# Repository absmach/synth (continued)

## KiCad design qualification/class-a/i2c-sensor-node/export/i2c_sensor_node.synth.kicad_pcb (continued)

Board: 2 copper layers, 57 parts (0 on the bottom side), 35 nets, no tracks yet.

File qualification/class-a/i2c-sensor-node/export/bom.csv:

refdes,value,kind,description,kicad_symbol,kicad_footprint,lcsc_pn,mpn
C1,10uF,capacitor,"Generic 0805 MLCC, X7R/X5R, any value",Device:C,Capacitor_SMD:C_0805_2012Metric,,
C10,100nF,capacitor,"Generic 0603 MLCC, X7R/X5R, any value",Device:C,Capacitor_SMD:C_0603_1608Metric,,
C11,100nF,capacitor,"Generic 0603 MLCC, X7R/X5R, any value",Device:C,Capacitor_SMD:C_0603_1608Metric,,
C12,100nF,capacitor,"Generic 0603 MLCC, X7R/X5R, any value",Device:C,Capacitor_SMD:C_0603_1608Metric,,
C2,10uF,capacitor,"Generic 0805 MLCC, X7R/X5R, any value",Device:C,Capacitor_SMD:C_0805_2012Metric,,
C3,47uF,capacitor,"47µF 16V tantalum capacitor, polarised, 3528 case",Device:C_Polarized,Capacitor_Tantalum_SMD:CP_EIA-3528-21_Kemet-B,,
C4,10uF,capacitor,"Generic 0805 MLCC, X7R/X5R, any value",Device:C,Capacitor_SMD:C_0805_2012Metric,,
C5,100nF,capacitor,"Generic 0603 MLCC, X7R/X5R, any value",Device:C,Capacitor_SMD:C_0603_1608Metric,,
C6,100nF,capacitor,"Generic 0603 MLCC, X7R/X5R, any value",Device:C,Capacitor_SMD:C_0603_1608Metric,,
C7,4.7uF,capacitor,"Generic 0603 MLCC, X7R/X5R, any value",Device:C,Capacitor_SMD:C_0603_1608Metric,,
C8,100nF,capacitor,"Generic 0603 MLCC, X7R/X5R, any value",Device:C,Capacitor_SMD:C_0603_1608Metric,,
D1,1N5819,diode,"Diodes Inc. 1N5819HW-7-F, 40 V 1 A Schottky diode, SOD-123, low forward voltage",Device:D_Schottky,Diode_SMD:D_SOD-123,C82544,1N5819HW-7-F
D10,3.3V zener,diode,"3.3V Zener diode, SOD-123",Device:D_Zener,Diode_SMD:D_SOD-123,,
D11,3.3V zener,diode,"3.3V Zener diode, SOD-123",Device:D_Zener,Diode_SMD:D_SOD-123,,
D12,3.3V zener,diode,"3.3V Zener diode, SOD-123",Device:D_Zener,Diode_SMD:D_SOD-123,,
D13,3.3V zener,diode,"3.3V Zener diode, SOD-123",Device:D_Zener,Diode_SMD:D_SOD-123,,
D14,1N5819,diode,"Diodes Inc. 1N5819HW-7-F, 40 V 1 A Schottky diode, SOD-123, low forward voltage",Device:D_Schottky,Diode_SMD:D_SOD-123,C82544,1N5819HW-7-F
D15,GREEN,diode,"Lite-On LTST-C190KGKT green AlInGaP LED, 0603, Vf 1.9 to 2.4V at 20mA",Device:LED,LED_SMD:LED_0603_1608Metric,,LTST-C190KGKT
D19,3.3V zener,diode,"3.3V Zener diode, SOD-123",Device:D_Zener,Diode_SMD:D_SOD-123,,
D20,3.3V zener,diode,"3.3V Zener diode, SOD-123",Device:D_Zener,Diode_SMD:D_SOD-123,,
D21,3.3V zener,diode,"3.3V Zener diode, SOD-123",Device:D_Zener,Diode_SMD:D_SOD-123,,
D22,3.3V zener,diode,"3.3V Zener diode, SOD-123",Device:D_Zener,Diode_SMD:D_SOD-123,,
D23,3.3V zener,diode,"3.3V Zener diode, SOD-123",Device:D_Zener,Diode_SMD:D_SOD-123,,
D24,3.3V zener,diode,"3.3V Zener diode, SOD-123",Device:D_Zener,Diode_SMD:D_SOD-123,,
D4,PTVS6V0S1UR,diode,"Nexperia PTVS6V0S1UR 400 W unidirectional TVS, 6.0 V standoff, SOD123W, for VBUS and CC",Device:D_Zener,Diode_SMD:Nexperia_CFP3_SOD-123W,,PTVS6V0S1UR
D7,3.3V zener,diode,"3.3V Zener diode, SOD-123",Device:D_Zener,Diode_SMD:D_SOD-123,,
D8,3.3V zener,diode,"3.3V Zener diode, SOD-123",Device:D_Zener,Diode_SMD:D_SOD-123,,
D9,3.3V zener,diode,"3.3V Zener diode, SOD-123",Device:D_Zener,Diode_SMD:D_SOD-123,,
F1,0.5A hold,fuse,"Resettable polyfuse (PPTC), 0.5 A hold, 2-pin, 1812. Generic: MPN needs sourcing.",Device:Polyfuse,Fuse:Fuse_1812_4532Metric,,
H2,(no value),mounting_hole,M2.5 non-plated mounting hole (NPTH) for a board corner,Mechanical:MountingHole,MountingHole:MountingHole_2.5mm,,
H3,(no value),mounting_hole,M2.5 non-plated mounting hole (NPTH) for a board corner,Mechanical:MountingHole,MountingHole:MountingHole_2.5mm,,
J1,JST S2B-XH-A-1,connector,"JST XH-series 2-pin wire-to-board connector, 2.0mm pitch",Connector_Generic:Conn_01x02,Connector_JST:JST_XH_S2B-XH-A-1_1x02_P2.50mm_Horizontal,,
J3,JST S4B-PH-K-S,connector,"JST PH-series 4-pin wire-to-board connector, 2.0mm pitch",Connector_Generic:Conn_01x04,Connector_JST:JST_PH_S4B-PH-K_1x04_P2.00mm_Horizontal,,
J4,SWD,connector,"1x5 through-hole pin header, 2.54 mm pitch (SWD); datasheet_url is the product page of the Harwin M20 series, no manufacturer PDF link was verifiable",Connector_Generic:Conn_01x05,Connector_PinHeader_2.54mm:PinHeader_1x05_P2.54mm_Vertical,,
J5,GPIO,connector,"1x12 through-hole pin header, 2.54 mm pitch (GPIO); datasheet_url is the product page of the Harwin M20 series, no manufacturer PDF link was verifiable",Connector_Generic:Conn_01x12,Connector_PinHeader_2.54mm:PinHeader_1x12_P2.54mm_Vertical,,
R10,4.7k,resistor,"Generic 0603 thick-film resistor, any value",Device:R_US,Resistor_SMD:R_0603_1608Metric,,
R11,330,resistor,"Generic 0603 thick-film resistor, any value",Device:R_US,Resistor_SMD:R_0603_1608Metric,,
R12,1k,resistor,"Generic 0603 thick-film resistor, any value",Device:R_US,Resistor_SMD:R_0603_1608Metric,,
R13,100,resistor,"Generic 0603 thick-film resistor, any value",Device:R_US,Resistor_SMD:R_0603_1608Metric,,
R14,100,resistor,"Generic 0603 thick-film resistor, any value",Device:R_US,Resistor_SMD:R_0603_1608Metric,,
R15,330,resistor,"Generic 0603 thick-film resistor, any value",Device:R_US,Resistor_SMD:R_0603_1608Metric,,
R16,330,resistor,"Generic 0603 thick-film resistor, any value",Device:R_US,Resistor_SMD:R_0603_1608Metric,,
R17,330,resistor,"Generic 0603 thick-film resistor, any value",Device:R_US,Resistor_SMD:R_0603_1608Metric,,
R18,330,resistor,"Generic 0603 thick-film resistor, any value",Device:R_US,Resistor_SMD:R_0603_1608Metric,,
R19,330,resistor,"Generic 0603 thick-film resistor, any value",Device:R_US,Resistor_SMD:R_0603_1608Metric,,
R20,330,resistor,"Generic 0603 thick-film resistor, any value",Device:R_US,Resistor_SMD:R_0603_1608Metric,,
R21,330,resistor,"Generic 0603 thick-film resistor, any value",Device:R_US,Resistor_SMD:R_0603_1608Metric,,
R22,330,resistor,"Generic 0603 thick-film resistor, any value",Device:R_US,Resistor_SMD:R_0603_1608Metric,,
R23,100,resistor,"Generic 0805 thick-film resistor, any value",Device:R_US,Resistor_SMD:R_0805_2012Metric,,
R24,680,resistor,"Generic 0603 thick-film resistor, any value",Device:R_US,Resistor_SMD:R_0603_1608Metric,,
R3,10k,resistor,"Generic 0603 thick-film resistor, any value",Device:R_US,Resistor_SMD:R_0603_1608Metric,,
R9,4.7k,resistor,"Generic 0603 thick-film resistor, any value",Device:R_US,Resistor_SMD:R_0603_1608Metric,,
SW1,RESET,switch,Generic SPST tactile button,Switch:SW_Push,Button_Switch_SMD:SW_SPST_PTS645Sx43SMTR92,,
U1,AMS1117-3.3,regulator,"AMS1117-3.3 fixed 3.3V LDO regulator, SOT-223 — common JLC stock",Regulator_Linear:AMS1117-3.3,Package_TO_SOT_SMD:SOT-223-3_TabPin2,C6186,AMS1117-3.3
U2,STM32G030F6P6,mcu,"STMicro STM32G030F6P6 Cortex-M0+ 64 MHz, 32 KB flash, 8 KB RAM, TSSOP-20. Pin map checked against KiCad MCU_ST_STM32G0:STM32G030F6Px",MCU_ST_STM32G0:STM32G030F6Px,Package_SO:TSSOP-20_4.4x6.5mm_P0.65mm,,STM32G030F6P6
U3,BME680,sensor,"Bosch BME680 T/RH/P/gas sensor, 3.0x3.0 mm 8-pin LGA, I2C/SPI. Pins checked against KiCad Sensor:BME680; footprint is the 3x3 mm 0.8 mm pitch one whose KiCad description cites the BME680 datasheet",Sensor:BME680,Package_LGA:Bosch_LGA-8_3x3mm_P0.8mm_ClockwisePinNumbering,,BME680
U5,24LC256-I/SN,memory,"Microchip 24LC256-I/SN 256 Kbit I2C EEPROM, SOIC-8. Pin map checked against KiCad Memory_EEPROM:24LC256",Memory_EEPROM:24LC256,Package_SO:SOIC-8_3.9x4.9mm_P1.27mm,C411625,24LC256-I/SN

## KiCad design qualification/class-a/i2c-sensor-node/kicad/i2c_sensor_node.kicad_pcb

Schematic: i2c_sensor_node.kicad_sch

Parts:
C1, C2, C4: 10uF; C_0805_2012Metric
C3: 47uF; CP_EIA-3528-21_Kemet-B
C5, C6, C8, C9, C10, C11, C12, C14: 100nF; C_0603_1608Metric
C7, C13: 4.7uF; C_0603_1608Metric
D1, D2, D14: 1N5819; D_SOD-123; MPN 1N5819; LCSC C8224
D3, D4: PTVS6V0S1UR; Nexperia_CFP3_SOD-123W; MPN PTVS6V0S1UR
D5, D6, D7, D8, D9, D10, D11, D12, D13: PRTR5V0U2X; SOT-143; MPN PRTR5V0U2X
D15: GREEN; LED_0603_1608Metric; MPN 0603-GREEN; LCSC C72043
D16: AMBER; LED_0603_1608Metric
D17: RED; LED_0603_1608Metric; MPN 0603-RED; LCSC C2286
D18: GREEN; LED_0603_1608Metric; MPN LTST-C190KGKT
F1, F2: 0.5A hold; Fuse_Bourns_MF-RG300
H1, H2, H3, H4: (no value); MountingHole_2.5mm
J1: JST S2B-XH-A-1; JST_XH_S2B-XH-A-1_1x02_P2.50mm_Horizontal
J2: TYPE-C-31-M-12; USB_C_Receptacle_HRO_TYPE-C-31-M-12; MPN TYPE-C-31-M-12; LCSC C165948
J3: JST S4B-PH-K-S; JST_PH_S4B-PH-K_1x04_P2.00mm_Horizontal
J4: SWD; PinHeader_1x05_P2.54mm_Vertical
J5: GPIO; PinHeader_1x12_P2.54mm_Vertical
Q1: IRLML6244; SOT-23
R1, R2: 5.1k; R_0603_1608Metric
R3, R6, R28: 10k; R_0603_1608Metric
R4, R7, R12, R26, R27: 1k; R_0603_1608Metric
R5, R8: 100k; R_0603_1608Metric
R9, R10: 4.7k; R_0603_1608Metric
R11, R15, R16, R17, R18, R19, R20, R21, R22: 330; R_0603_1608Metric
R13, R14: 100; R_0603_1608Metric
R23: 100; R_0805_2012Metric
R24, R25: 680; R_0603_1608Metric
SW1: RESET; SW_SPST_PTS645Sx43SMTR92
TP1: +5V_PROT; TestPoint_Pad_D1.5mm
TP2: +3V3; TestPoint_Pad_D1.5mm
TP3, TP9: GND; TestPoint_Pad_D1.5mm
TP4: I2C_SDA; TestPoint_Pad_D1.5mm
TP5: I2C_SCL; TestPoint_Pad_D1.5mm
TP6: UART_TX; TestPoint_Pad_D1.5mm
TP7: UART_RX; TestPoint_Pad_D1.5mm
TP8: VIN_FUSED; TestPoint_Pad_D1.5mm
U1: AMS1117-3.3; SOT-223-3_TabPin2; MPN AMS1117-3.3; LCSC C6186
U2: STM32G030F6P6; TSSOP-20_4.4x6.5mm_P0.65mm; MPN STM32G030F6P6
U3: BME680; Bosch_LGA-8_3x3mm_P0.8mm_ClockwisePinNumbering; MPN BME680
U4: CH340C; SOIC-16_3.9x9.9mm_P1.27mm; MPN CH340C
U5: 24LC256-I/SN; SOIC-8_3.9x4.9mm_P1.27mm; MPN 24LC256-I/SN; LCSC C7611

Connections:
3V3_REF: J3.4, J4.1, J5.1, R23.2
+3V3: C3.1, C4.1, C5.1, C6.1, C7.1, C9.1, C10.1, C11.1, C12.1, D7.4 (VCC), D8.4 (VCC), D9.4 (VCC), D10.4 (VCC), D11.4 (VCC), D12.4 (VCC), D13.4 (VCC), D14.2 (A), R3.1, R5.1, R6.1, R9.1, R10.1, R24.1, R26.1, R27.1, R28.1, TP2.1, U1.2 (VO), U2.4 (VDD), U3.2 (CSB), U3.6 (VDDIO), U3.8 (VDD), U4.4 (V3), U4.16 (VCC), U5.8 (VCC)
+5V_PROT: C1.1, C2.1, D1.1 (K), D2.1 (K), D4.1 (K), TP1.1, U1.3 (VI)
BOOT_DRV: Q1.3 (D), R6.2, R7.1
BRIDGE_RXD: D18.1 (K), U2.16 (PA9/PA11), U4.3 (RXD)
BRIDGE_TXD: D17.1 (K), U2.17 (PA10/PA12), U4.2 (TXD)
CH340_STRAP: R28.2, U4.9 (~CTS), U4.10 (~DSR), U4.11 (~RI), U4.12 (~DCD), U4.15 (R232)
DTR_N: R4.1, U4.13 (~DTR)
GND: C1.2, C2.2, C3.2, C4.2, C5.2, C6.2, C7.2, C8.2, C9.2, C10.2, C11.2, C12.2, C13.2, C14.2, D3.2 (A), D4.2 (A), D5.1 (GND), D6.1 (GND), D7.1 (GND), D8.1 (GND), D9.1 (GND), D10.1 (GND), D11.1 (GND), D12.1 (GND), D13.1 (GND), D15.1 (K), D16.1 (K), J1.2, J2.A1 (GND), J2.A12 (GND), J2.B1 (GND), J2.B12 (GND), J2.SH (SHIELD), J3.1, J4.4, J5.2, J5.6, J5.10, Q1.2 (S), R1.2, R2.2, R8.2, SW1.2, TP3.1, TP9.1, U1.1 (GND), U2.5 (VSS), U3.1 (GND), U3.5 (SDO), U3.7 (GND), U4.1 (GND), U5.1 (A0), U5.2 (A1), U5.3 (A2), U5.4 (GND), U5.7 (WP)
GPIO_PA0: D10.2 (I/O1), J5.3, R15.2
GPIO_PA0_MCU: R15.1, U2.7 (PA0)
GPIO_PA1: D10.3 (I/O2), J5.4, R16.2
GPIO_PA1_MCU: R16.1, U2.8 (PA1)
GPIO_PA4: D11.2 (I/O1), J5.5, R17.2
GPIO_PA4_MCU: R17.1, U2.11 (PA4)
GPIO_PA5: D11.3 (I/O2), J5.7, R18.2
GPIO_PA5_MCU: R18.1, U2.12 (PA5)
GPIO_PA6: D12.2 (I/O1), J5.8, R19.2
GPIO_PA6_MCU: R19.1, U2.13 (PA6)
GPIO_PA7: D12.3 (I/O2), J5.9, R20.2
GPIO_PA7_MCU: R20.1, U2.14 (PA7)
GPIO_PB0: D13.2 (I/O1), J5.11, R21.2
GPIO_PB0_MCU: R21.1, U2.15 (PA8/PB0/PB1/PB2)
GPIO_PB9: D13.3 (I/O2), J5.12, R22.2
GPIO_PB9_MCU: R22.1, U2.2 (PB9/PC14)
I2C_SCL: R10.2, TP5.1, U2.20 (PB3/PB4/PB5/PB6), U3.4 (SCK), U5.6 (SCL)
I2C_SDA: R9.2, TP4.1, U2.1 (PB7/PB8), U3.3 (SDI), U5.5 (SDA)
LED_PWR: D15.2 (A), R24.2
LED_RXA: D18.2 (A), R27.2
LED_STATUS: R25.1, U2.3 (PC15)
LED_STATUS_A: D16.2 (A), R25.2
LED_TXA: D17.2 (A), R26.2
NRST: C8.1, D9.2 (I/O1), J4.5, R3.2, R4.2, SW1.1, U2.6 (NRST)
REF_D: D14.1 (K), R23.1
RTS_N: Q1.1 (G), R5.2, U4.14 (~RTS)
SWCLK: D8.3 (I/O2), J4.3, R14.2
SWCLK_MCU: R7.2, R8.1, R14.1, U2.19 (PA14/PA15)
SWDIO: D8.2 (I/O1), J4.2, R13.2
SWDIO_MCU: R13.1, U2.18 (PA13)
U2_RX: R12.1, U2.10 (PA3)
U2_TX: R11.1, U2.9 (PA2)
UART_RX: D7.3 (I/O2), J3.3, R12.2, TP7.1
UART_TX: D7.2 (I/O1), J3.2, R11.2, TP6.1
USB_CC1: D6.2 (I/O1), J2.A5 (CC1), R1.1
USB_CC2: D6.3 (I/O2), J2.B5 (CC2), R2.1
USB_DN: D5.3 (I/O2), J2.A7 (D-), J2.B7 (D-), U4.6 (UD-)
USB_DP: D5.2 (I/O1), J2.A6 (D+), J2.B6 (D+), U4.5 (UD+)
VBUS_FUSED: C13.1, D2.2 (A), F2.2
VBUS_USB: C14.1, D3.1 (K), D5.4 (VCC), D6.4 (VCC), F2.1, J2.A4 (VBUS), J2.A9 (VBUS), J2.B4 (VBUS), J2.B9 (VBUS)
VIN_5V_FUSED: D1.2 (A), F1.2, TP8.1
VIN_5V_RAW: F1.1, J1.1

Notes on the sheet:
5V INPUT: FUSE THEN DIODE
USB-C
3V3 REGULATOR
STM32G030 MCU
USB BRIDGE
I2C SENSING
UART BREAKOUT
GPIO HEADER
TEST POINTS
J1 pin 1 = +5 V, pin 2 = GND. Mates with JST XHP-2 housing.
Order: fuse first (fault current meets a limiter), diode second (reversed supply meets a blocker).
D4 clamps transients on +5V_PROT, behind D1 so a reversed supply never forward-biases it.
CC1/CC2 5.1k to GND: advertises a 5 V sink. D5 guards D+/D-, D6 the CC pins, D3 VBUS.
D2 ORs VBUS onto +5V_PROT and blocks back-feed into the host port.
Two sources: the higher of the two diode-OR inputs supplies the board; neither is back-fed.
AMS1117 tab is VOUT (pin 2): the tab pad is the +3V3 copper area.
Power LED: (3.3 V - 2.2 V) / 680 R = 1.6 mA.
J4: 1 = 3V3_REF (sense only), 2 = SWDIO, 3 = SWCLK, 4 = GND, 5 = NRST.
PA14 is SWCLK and BOOT0. Default option bytes (nBOOT_SEL=1) ignore the pin; blank flash enters the ROM bootloader.
Status LED on PC15: (3.3 - 2.0) / 680 = 1.9 mA.
CH340C has an internal oscillator: no crystal. VCC = V3 = 3.3 V.
CTS, DSR, RI, DCD and R232 are tied high through R28 (modem lines unused).
DTR (active low) pulls NRST low through 1k. RTS asserted (low) turns Q1 off and BOOT0 rises to 3.3 V.
Idle RTS is high, Q1 on, BOOT0 low: boots flash with the bridge attached or not.
D17 lights on host-to-MCU data, D18 on MCU-to-host data.
BME680 SDO low = 0x76, CSB high = I2C. 24LC256 A2:A0 low = 0x50. No collision.
One pull-up pair, 4.7k each, for the whole bus.
J3: 1 GND, 2 UART_TX (MCU out), 3 UART_RX (MCU in), 4 3V3_REF (sense only, 3 mA max).
Host must use 3.3 V logic. Clamp to +3V3 + one diode drop (about 4.0 V) and to GND - 0.7 V.
J5: 1 3V3_REF, 2 GND, 3 PA0, 4 PA1, 5 PA4, 6 GND, 7 PA5, 8 PA6, 9 PA7, 10 GND, 11 PB0, 12 PB9.
3V3_REF = +3V3 through D14 (blocks back-drive) and 100R: sense or reference only, 3 mA max (about 2.7 V at 3 mA), 30 mA into a short.
TP1 +5V_PROT, TP2 +3V3, TP3/TP9 GND, TP4 I2C_SDA, TP5 I2C_SCL, TP6 UART_TX, TP7 UART_RX, TP8 VIN_5V_FUSED.
H1-H4: M2.5 non-plated mounting holes at the corners.

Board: 2 copper layers, 87 parts (0 on the bottom side), 51 nets, no tracks yet.

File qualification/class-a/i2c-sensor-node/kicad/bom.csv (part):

refdes,value,kind,description,kicad_symbol,kicad_footprint,lcsc_pn,mpn
C1,10uF,capacitor,"Generic 0805 MLCC, X7R/X5R, any value",Device:C,Capacitor_SMD:C_0805_2012Metric,,
C10,100nF,capacitor,"Generic 0603 MLCC, X7R/X5R, any value",Device:C,Capacitor_SMD:C_0603_1608Metric,,
C11,100nF,capacitor,"Generic 0603 MLCC, X7R/X5R, any value",Device:C,Capacitor_SMD:C_0603_1608Metric,,
C12,100nF,capacitor,"Generic 0603 MLCC, X7R/X5R, any value",Device:C,Capacitor_SMD:C_0603_1608Metric,,
C13,4.7uF,capacitor,"Generic 0603 MLCC, X7R/X5R, any value",Device:C,Capacitor_SMD:C_0603_1608Metric,,
C14,100nF,capacitor,"Generic 0603 MLCC, X7R/X5R, any value",Device:C,Capacitor_SMD:C_0603_1608Metric,,
C2,10uF,capacitor,"Generic 0805 MLCC, X7R/X5R, any value",Device:C,Capacitor_SMD:C_0805_2012Metric,,
C3,47uF,capacitor,"47µF 16V tantalum capacitor, polarised, 3528 case",Device:C_Polarized,Capacitor_Tantalum_SMD:CP_EIA-3528-21_Kemet-B,,
C4,10uF,capacitor,"Generic 0805 MLCC, X7R/X5R, any value",Device:C,Capacitor_SMD:C_0805_2012Metric,,
C5,100nF,capacitor,"Generic 0603 MLCC, X7R/X5R, any value",Device:C,Capacitor_SMD:C_0603_1608Metric,,
C6,100nF,capacitor,"Generic 0603 MLCC, X7R/X5R, any value",Device:C,Capacitor_SMD:C_0603_1608Metric,,
C7,4.7uF,capacitor,"Generic 0603 MLCC, X7R/X5R, any value",Device:C,Capacitor_SMD:C_0603_1608Metric,,
C8,100nF,capacitor,"Generic 0603 MLCC, X7R/X5R, any value",Device:C,Capacitor_SMD:C_0603_1608Metric,,
C9,100nF,capacitor,"Generic 0603 MLCC, X7R/X5R, any value",Device:C,Capacitor_SMD:C_0603_1608Metric,,
D1,1N5819,diode,"Generic Schottky diode (SS14-class), low forward voltage",Device:D_Schottky,Diode_SMD:D_SOD-123,C8224,1N5819
D10,PRTR5V0U2X,diode,"Nexperia PRTR5V0U2X ultra low capacitance (1 pF) 2-line rail-to-rail ESD protection for USB 2.0 data lines, SOT143B",Power_Protection:PRTR5V0U2X,Package_TO_SOT_SMD:SOT-143,,PRTR5V0U2X
D11,PRTR5V0U2X,diode,"Nexperia PRTR5V0U2X ultra low capacitance (1 pF) 2-line rail-to-rail ESD protection for USB 2.0 data lines, SOT143B",Power_Protection:PRTR5V0U2X,Package_TO_SOT_SMD:SOT-143,,PRTR5V0U2X
D12,PRTR5V0U2X,diode,"Nexperia PRTR5V0U2X ultra low capacitance (1 pF) 2-line rail-to-rail ESD protection for USB 2.0 data lines, SOT143B",Power_Protection:PRTR5V0U2X,Package_TO_SOT_SMD:SOT-143,,PRTR5V0U2X
D13,PRTR5V0U2X,diode,"Nexperia PRTR5V0U2X ultra low capacitance (1 pF) 2-line rail-to-rail ESD protection for USB 2.0 data lines, SOT143B",Power_Protection:PRTR5V0U2X,Package_TO_SOT_SMD:SOT-143,,PRTR5V0U2X
D14,1N5819,diode,"Generic Schottky diode (SS14-class), low forward voltage",Device:D_Schottky,Diode_SMD:D_SOD-123,C8224,1N5819
D15,GREEN,diode,"Green LED, 0603 package, ~2.2V Vf",Device:LED,LED_SMD:LED_0603_1608Metric,C72043,0603-GREEN
D16,AMBER,diode,"Amber surface-mount LED, 0603",Device:LED,LED_SMD:LED_0603_1608Metric,,
D17,RED,diode,"Red LED, 0603 package, ~2.0V Vf",Device:LED,LED_SMD:LED_0603_1608Metric,C2286,0603-RED
D18,GREEN,diode,"Lite-On LTST-C190KGKT green AlInGaP LED, 0603, Vf 1.9 to 2.4V at 20mA",Device:LED,LED_SMD:LED_0603_1608Metric,,LTST-C190KGKT
D2,1N5819,diode,"Generic Schottky diode (SS14-class), low forward voltage",Device:D_Schottky,Diode_SMD:D_SOD-123,C8224,1N5819
D3,PTVS6V0S1UR,diode,"Nexperia PTVS6V0S1UR 400 W unidirectional TVS, 6.0 V standoff, SOD123W, for VBUS and CC",Device:D_Zener,Diode_SMD:Nexperia_CFP3_SOD-123W,,PTVS6V0S1UR
D4,PTVS6V0S1UR,diode,"Nexperia PTVS6V0S1UR 400 W unidirectional TVS, 6.0 V standoff, SOD123W, for VBUS and CC",Device:D_Zener,Diode_SMD:Nexperia_CFP3_SOD-123W,,PTVS6V0S1UR
D5,PRTR5V0U2X,diode,"Nexperia PRTR5V0U2X ultra low capacitance (1 pF) 2-line rail-to-rail ESD protection for USB 2.0 data lines, SOT143B",Power_Protection:PRTR5V0U2X,Package_TO_SOT_SMD:SOT-143,,PRTR5V0U2X
D6,PRTR5V0U2X,diode,"Nexperia PRTR5V0U2X ultra low capacitance (1 pF) 2-line rail-to-rail ESD protection for USB 2.0 data lines, SOT143B",Power_Protection:PRTR5V0U2X,Package_TO_SOT_SMD:SOT-143,,PRTR5V0U2X
D7,PRTR5V0U2X,diode,"Nexperia PRTR5V0U2X ultra low capacitance (1 pF) 2-line rail-to-rail ESD protection for USB 2.0 data lines, SOT143B",Power_Protection:PRTR5V0U2X,Package_TO_SOT_SMD:SOT-143,,PRTR5V0U2X
D8,PRTR5V0U2X,diode,"Nexperia PRTR5V0U2X ultra low capacitance (1 pF) 2-line rail-to-rail ESD protection for USB 2.0 data lines, SOT143B",Power_Protection:PRTR5V0U2X,Package_TO_SOT_SMD:SOT-143,,PRTR5V0U2X
D9,PRTR5V0U2X,diode,"Nexperia PRTR5V0U2X ultra low capacitance (1 pF) 2-line rail-to-rail ESD protection for USB 2.0 data lines, SOT143B",Power_Protection:PRTR5V0U2X,Package_TO_SOT_SMD:SOT-143,,PRTR5V0U2X
F1,0.5A hold,fuse,"Resettable polyfuse (PPTC), 2-pin",Device:Polyfuse,Fuse:Fuse_Bourns_MF-RG300,,
F2,0.5A hold,fuse,"Resettable polyfuse (PPTC), 2-pin",Device:Polyfuse,Fuse:Fuse_Bourns_MF-RG300,,
H1,(no value),mounting_hole,M2.5 non-plated mounting hole (NPTH) for a board corner,Mechanical:MountingHole,MountingHole:MountingHole_2.5mm,,
H2,(no value),mounting_hole,M2.5 non-plated mounting hole (NPTH) for a board corner,Mechanical:MountingHole,MountingHole:MountingHole_2.5mm,,
H3,(no value),mounting_hole,M2.5 non-plated mounting hole (NPTH) for a board corner,Mechanical:MountingHole,MountingHole:MountingHole_2.5mm,,
H4,(no value),mounting_hole,M2.5 non-plated mounting hole (NPTH) for a board corner,Mechanical:MountingHole,MountingHole:MountingHole_2.5mm,,
J1,JST S2B-XH-A-1,connector,"JST XH-series 2-pin wire-to-board connector, 2.0mm pitch",Connector_Generic:Conn_01x02,Connector_JST:JST_XH_S2B-XH-A-1_1x02_P2.50mm_Horizontal,,
J2,TYPE-C-31-M-12,connector,"USB-C receptacle, 24-pin SMD. Modelled here with primary and mirrored power/ground/data pins for full pad coverage.",Connector:USB_C_Receptacle,Connector_USB:USB_C_Receptacle_HRO_TYPE-C-31-M-12,C165948,TYPE-C-31-M-12
J3,JST S4B-PH-K-S,connector,"JST PH-series 4-pin wire-to-board connector, 2.0mm pitch",Connector_Generic:Conn_01x04,Connector_JST:JST_PH_S4B-PH-K_1x04_P2.00mm_Horizontal,,
J4,SWD,connector,"1x5 through-hole pin header, 2.54 mm pitch (SWD)",Connector_Generic:Conn_01x05,Connector_PinHeader_2.54mm:PinHeader_1x05_P2.54mm_Vertical,,
J5,GPIO,connector,"1x12 through-hole pin header, 2.54 mm pitch (GPIO)",Connector_Generic:Conn_01x12,Connector_PinHeader_2.54mm:PinHeader_1x12_P2.54mm_Vertical,,
Q1,IRLML6244,transistor,"IR IRLML6244 logic-level N-channel MOSFET, SOT-23",Transistor_FET:IRLML6244,Package_TO_SOT_SMD:SOT-23,,
R1,5.1k,resistor,"Generic 0603 thick-film resistor, any value",Device:R_US,Resistor_SMD:R_0603_1608Metric,,
R10,4.7k,resistor,"Generic 0603 thick-film resistor, any value",Device:R_US,Resistor_SMD:R_0603_1608Metric,,
R11,330,resistor,"Generic 0603 thick-film resistor, any value",Device:R_US,Resistor_SMD:R_0603_1608Metric,,
R12,1k,resistor,"Generic 0603 thick-film resistor, any value",Device:R_US,Resistor_SMD:R_0603_1608Metric,,
R13,100,resistor,"Generic 0603 thick-film resistor, any value",Device:R_US,Resistor_SMD:R_0603_1608Metric,,
R14,100,resistor,"Generic 0603 thick-film resistor, any value",Device:R_US,Resistor_SMD:R_0603_1608Metric,,
R15,330,resistor,"Generic 0603 thick-film resistor, any value",Device:R_US,Resistor_SMD:R_0603_1608Metric,,
R16,330,resistor,"Generic 0603 thick-film resistor, any value",Device:R_US,Resistor_SMD:R_0603_1608Metric,,
R17,330,resistor,"Generic 0603 thick-film resistor, any value",Device:R_US,Resistor_SMD:R_0603_1608Metric,,
R18,330,resistor,"Generic 0603 thick-film resistor, any value",Device:R_US,Resistor_SMD:R_0603_1608Metric,,
R19,330,resistor,"Generic 0603 thick-film resistor, any value",Device:R_US,Resistor_SMD:R_0603_1608Metric,,
R2,5.1k,resistor,"Generic 0603 thick-film resistor, any value",Device:R_US,Resistor_SMD:R_0603_1608Metric,,
R20,330,resistor,"Generic 0603 thick-film resistor, any value",Device:R_US,Resistor_SMD:R_0603_1608Metric,,
R21,330,resistor,"Generic 0603 thick-film resistor, any value",Device:R_US,Resistor_SMD:R_0603_1608Metric,,
R22,330,resistor,"Generic 0603 thick-film resistor, any value",Device:R_US,Resistor_SMD:R_0603_1608Metric,,
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
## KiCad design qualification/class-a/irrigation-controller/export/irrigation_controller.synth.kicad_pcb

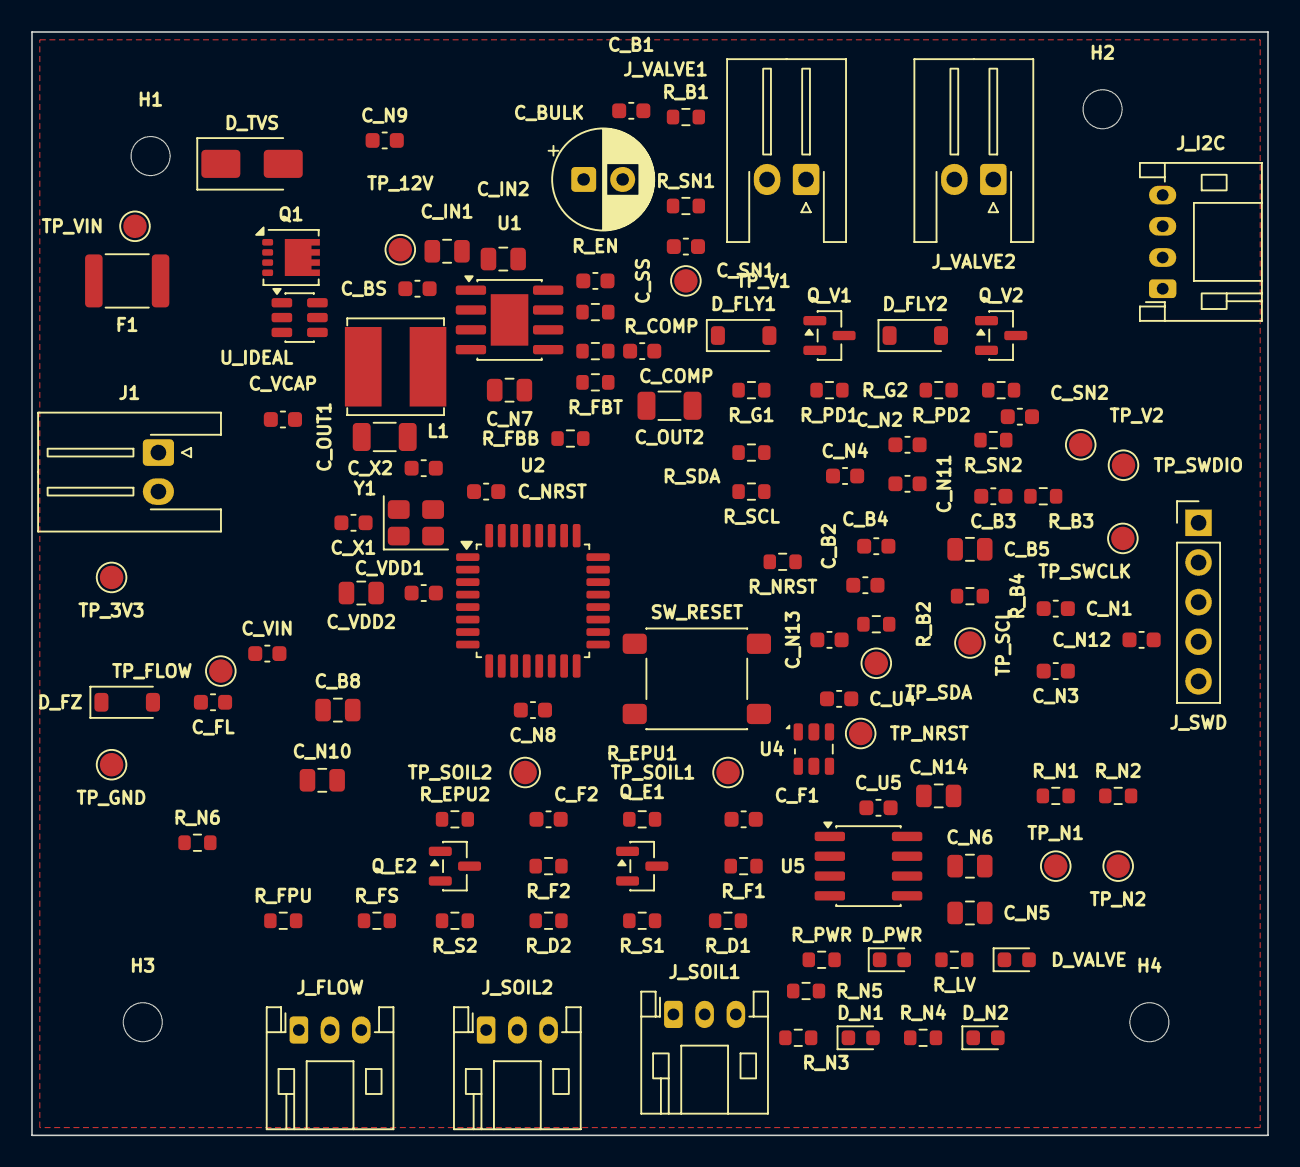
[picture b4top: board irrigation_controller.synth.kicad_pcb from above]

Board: 2 copper layers, 79.2 x 70.7 mm, 127 parts (0 on the bottom side), 46 nets, no tracks yet.

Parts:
C_B1, C_B2, C_B3, C_B4: 100nF; C_0603_1608Metric
C_B5, C_B8: 4.7uF; C_0805_2012Metric
C_BS: 10nF; C_0603_1608Metric
C_BULK: 100uF 25V; CP_Radial_D6.3mm_P2.50mm
C_COMP: 4.7nF; C_0603_1608Metric
C_F1, C_F2: 10nF; C_0603_1608Metric
C_FL: 10nF; C_0603_1608Metric
C_IN1, C_IN2: 10uF 25V; C_0805_2012Metric
C_N1, C_N2, C_N3, C_N4, C_N8, C_N9, C_N11, C_N12, C_N13: 100nF; C_0603_1608Metric
C_N5: 10uF; C_0805_2012Metric
C_N6, C_N10, C_N14: 4.7uF; C_0805_2012Metric
C_N7: 10uF 25V; C_0805_2012Metric
C_NRST: 100nF; C_0603_1608Metric
C_OUT1, C_OUT2: 22uF 10V; C_1206_3216Metric
C_SN1, C_SN2: 10nF; C_0603_1608Metric
C_SS: 100nF; C_0603_1608Metric
C_U4, C_U5: 100nF; C_0603_1608Metric
C_VCAP: 100nF; C_0603_1608Metric
C_VDD1: 100nF; C_0603_1608Metric
C_VDD2: 4.7uF; C_0805_2012Metric
C_VIN: 100nF; C_0603_1608Metric
C_X1, C_X2: 6.2pF; C_0603_1608Metric
D_FLY1, D_FLY2: 1N5819HW-7-F; D_SOD-123
D_FZ: (no value); D_SOD-123
D_N1: (no value); LED_0603_1608Metric
D_N2: LTST-C190KGKT; LED_0603_1608Metric
D_PWR: LTST-C190KGKT; LED_0603_1608Metric
D_TVS: SMAJ13A; D_SMA
D_VALVE: (no value); LED_0603_1608Metric
F1: 1812L150/16DR; Fuse_1812_4532Metric
H1, H2, H3, H4: (no value); MountingHole_2.5mm
J1: S2B-XH-A-1(LF)(SN); JST_XH_S2B-XH-A-1_1x02_P2.50mm_Horizontal
J_FLOW: S3B-PH-K-S(LF)(SN); JST_PH_S3B-PH-K_1x03_P2.00mm_Horizontal
J_I2C: S4B-PH-K-S(LF)(SN); JST_PH_S4B-PH-K_1x04_P2.00mm_Horizontal
J_SOIL1, J_SOIL2: S3B-PH-K-S(LF)(SN); JST_PH_S3B-PH-K_1x03_P2.00mm_Horizontal
J_SWD: (no value); PinHeader_1x05_P2.54mm_Vertical
J_VALVE1, J_VALVE2: S2B-XH-A-1(LF)(SN); JST_XH_S2B-XH-A-1_1x02_P2.50mm_Horizontal
L1: SRN6045TA-100M; L_Bourns_SRN6045TA
Q1: DMT6007LFG-7; Diodes_PowerDI3333-8
Q_E1, Q_E2: SI2301CDS-T1-GE3; SOT-23
Q_V1, Q_V2: AO3400A; SOT-23
R_B1, R_B2: 100k; R_0603_1608Metric
R_B3, R_B4: 47k; R_0603_1608Metric
R_COMP: 5.6k; R_0603_1608Metric
R_D1, R_D2: 10k; R_0603_1608Metric
R_EN: 100k; R_0603_1608Metric
R_EPU1, R_EPU2: 100k; R_0603_1608Metric
R_F1, R_F2: 1k; R_0603_1608Metric
R_FBB: 10k; R_0603_1608Metric
R_FBT: 26.1k; R_0603_1608Metric
R_FPU: 10k; R_0603_1608Metric
R_FS: 2.2k; R_0603_1608Metric
R_G1, R_G2: 100; R_0603_1608Metric
R_LV: 680; R_0603_1608Metric
R_N1, R_N5, R_N6: 100k; R_0603_1608Metric
R_N2: 47k; R_0603_1608Metric
R_N3: 2.2k; R_0603_1608Metric
R_N4: 680; R_0603_1608Metric
R_NRST: 10k; R_0603_1608Metric
R_PD1, R_PD2: 100k; R_0603_1608Metric
R_PWR: 680; R_0603_1608Metric
R_S1, R_S2: 1k; R_0603_1608Metric
R_SCL: 4.7k; R_0603_1608Metric
R_SDA: 4.7k; R_0603_1608Metric
R_SN1, R_SN2: 100; R_0603_1608Metric
SW_RESET: PTS645SM43SMTR92 LFS; SW_SPST_PTS645Sx43SMTR92
TP_3V3, TP_12V: (no value); TestPoint_Pad_D1.5mm
TP_FLOW: (no value); TestPoint_Pad_D1.5mm
TP_GND: (no value); TestPoint_Pad_D1.5mm
TP_N1, TP_N2: (no value); TestPoint_Pad_D1.5mm
TP_NRST: (no value); TestPoint_Pad_D1.5mm
TP_SCL: (no value); TestPoint_Pad_D1.5mm
TP_SDA: (no value); TestPoint_Pad_D1.5mm
TP_SOIL1, TP_SOIL2: (no value); TestPoint_Pad_D1.5mm
TP_SWCLK: (no value); TestPoint_Pad_D1.5mm
TP_SWDIO: (no value); TestPoint_Pad_D1.5mm
TP_V1, TP_V2: (no value); TestPoint_Pad_D1.5mm
TP_VIN: (no value); TestPoint_Pad_D1.5mm
U1: MP2307DN-LF-Z; SOIC-8-1EP_3.9x4.9mm_P1.27mm_EP2.41x3.3mm
U2: (no value); LQFP-32_7x7mm_P0.8mm
U4: (no value); Broadcom_APDS-9301
U5: 24LC256-I/SN; SOIC-8_3.9x4.9mm_P1.27mm
U_IDEAL: LM74700QDBVRQ1; SOT-23-6
Y1: 3TJ480000FYLBC; Crystal_SMD_3225-4Pin_3.2x2.5mm

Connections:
+3V3: C_B2.1, C_B4.1, C_B5.1, C_B8.1, C_N1.1, C_N2.1, C_N3.1, C_N4.1, C_N5.1, C_N6.1, C_N8.1, C_N10.1, C_N11.1, C_N12.1, C_N13.1, C_N14.1, C_OUT1.1, C_OUT2.1, C_U4.1, C_U5.1, C_VDD1.1, C_VDD2.1, J_I2C.2, J_SWD.1, L1.2, Q_E1.2, Q_E2.2, R_B2.1, R_B4.1, R_EPU1.1, R_EPU2.1, R_FBT.1, R_FPU.1, R_N1.1, R_N2.1, R_N4.1, R_NRST.1, R_PWR.1, R_SCL.1, R_SDA.1, TP_3V3.1, TP_N1.1, U2.4, U4.1, U5.8
+12V_VALVE: C_B1.1, C_B3.1, C_BULK.1, C_IN1.1, C_IN2.1, C_N7.1, C_N9.1, D_FLY1.1, D_FLY2.1, J_FLOW.1, J_VALVE1.1, J_VALVE2.1, Q1.5, R_B1.1, R_B3.1, R_EN.1, R_N3.1, R_N5.1, R_N6.1, R_SN1.1, R_SN2.1, TP_12V.1, U1.2, U_IDEAL.4
BUCK_BS: C_BS.1, U1.1
BUCK_COMP: R_COMP.1, U1.6
BUCK_COMPC: C_COMP.1, R_COMP.2
BUCK_EN: R_EN.2, U1.7
BUCK_FB: R_FBB.1, R_FBT.2, U1.5
BUCK_SS: C_SS.1, U1.8
BUCK_SW: C_BS.2, L1.1, U1.3
FLOW_IN: J_FLOW.3, R_FPU.2, R_FS.1
FLOW_PULSE: C_FL.1, D_FZ.1, R_FS.2, TP_FLOW.1, U2.13
GND: C_B1.2, C_B2.2, C_B3.2, C_B4.2, C_B5.2, C_B8.2, C_BULK.2, C_COMP.2, C_F1.2, C_F2.2, C_FL.2, C_IN1.2, C_IN2.2, C_N1.2, C_N2.2, C_N3.2, C_N4.2, C_N5.2, C_N6.2, C_N7.2, C_N8.2, C_N9.2, C_N10.2, C_N11.2, C_N12.2, C_N13.2, C_N14.2, C_NRST.2, C_OUT1.2, C_OUT2.2, C_SS.2, C_U4.2, C_U5.2, C_VDD1.2, C_VDD2.2, C_VIN.2, C_X1.2, C_X2.2, D_FZ.2, D_N1.1, D_N2.1, D_PWR.1, D_TVS.2, D_VALVE.1, J1.2, J_FLOW.2, J_I2C.1, J_SOIL1.3, J_SOIL2.3, J_SWD.3, Q_V1.2, Q_V2.2, R_B1.2, R_B2.2, R_B3.2, R_B4.2, R_D1.2, R_D2.2, R_FBB.2, R_N1.2, R_N2.2, R_N5.2, R_N6.2, R_PD1.2, R_PD2.2, SW_RESET.2, TP_GND.1, TP_N2.1, U1.4, U1.9, U2.5, U4.2, U4.3, U5.1, U5.2, U5.3, U5.4, U5.7, U_IDEAL.2, Y1.2, Y1.4
I2C_SCL: J_I2C.4, R_SCL.2, TP_SCL.1, U2.30, U4.4, U5.6
I2C_SDA: J_I2C.3, R_SDA.2, TP_SDA.1, U2.31, U4.5, U5.5
ID_VCAP: C_VCAP.1, U_IDEAL.1
LED_N12_A: D_N1.2, R_N3.2
LED_N33_A: D_N2.2, R_N4.2
LED_PWR_A: D_PWR.2, R_PWR.2
LED_VALVE_A: D_VALVE.2, R_LV.2
LED_VALVE_DRV: R_LV.1, U2.14
NRST: C_NRST.1, J_SWD.5, R_NRST.2, SW_RESET.1, TP_NRST.1, U2.6
OSC_IN: C_X1.1, U2.2, Y1.1
OSC_OUT: C_X2.1, U2.3, Y1.3
Q1_GATE: Q1.4, U_IDEAL.5
SNUB1: C_SN1.1, R_SN1.2
SNUB2: C_SN2.1, R_SN2.2
SOIL1_ADC: C_F1.1, R_F1.2, TP_SOIL1.1, U2.9
SOIL1_EXC: Q_E1.3, R_S1.1
SOIL1_EXC_EN: Q_E1.1, R_EPU1.2, U2.11
SOIL1_PROBE: J_SOIL1.1, R_S1.2
SOIL1_SENSE: J_SOIL1.2, R_D1.1, R_F1.1
SOIL2_ADC: C_F2.1, R_F2.2, TP_SOIL2.1, U2.10
SOIL2_EXC: Q_E2.3, R_S2.1
SOIL2_EXC_EN: Q_E2.1, R_EPU2.2, U2.12
SOIL2_PROBE: J_SOIL2.1, R_S2.2
SOIL2_SENSE: J_SOIL2.2, R_D2.1, R_F2.1
SWCLK: J_SWD.4, TP_SWCLK.1, U2.25
SWDIO: J_SWD.2, TP_SWDIO.1, U2.24
VALVE1_GATE: R_G1.1, U2.27
VALVE1_GATE_Q: Q_V1.1, R_G1.2, R_PD1.1
VALVE1_SW: C_SN1.2, D_FLY1.2, J_VALVE1.2, Q_V1.3, TP_V1.1
VALVE2_GATE: R_G2.1, U2.28
VALVE2_GATE_Q: Q_V2.1, R_G2.2, R_PD2.1
VALVE2_SW: C_SN2.2, D_FLY2.2, J_VALVE2.2, Q_V2.3, TP_V2.1
VIN_12V_RAW: F1.1, J1.1
VIN_FUSED: C_VCAP.2, C_VIN.1, D_TVS.1, F1.2, Q1.1, Q1.2, Q1.3, TP_VIN.1, U_IDEAL.3, U_IDEAL.6
